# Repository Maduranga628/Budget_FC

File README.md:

# Budget_FC
Low Cost Flight Controller

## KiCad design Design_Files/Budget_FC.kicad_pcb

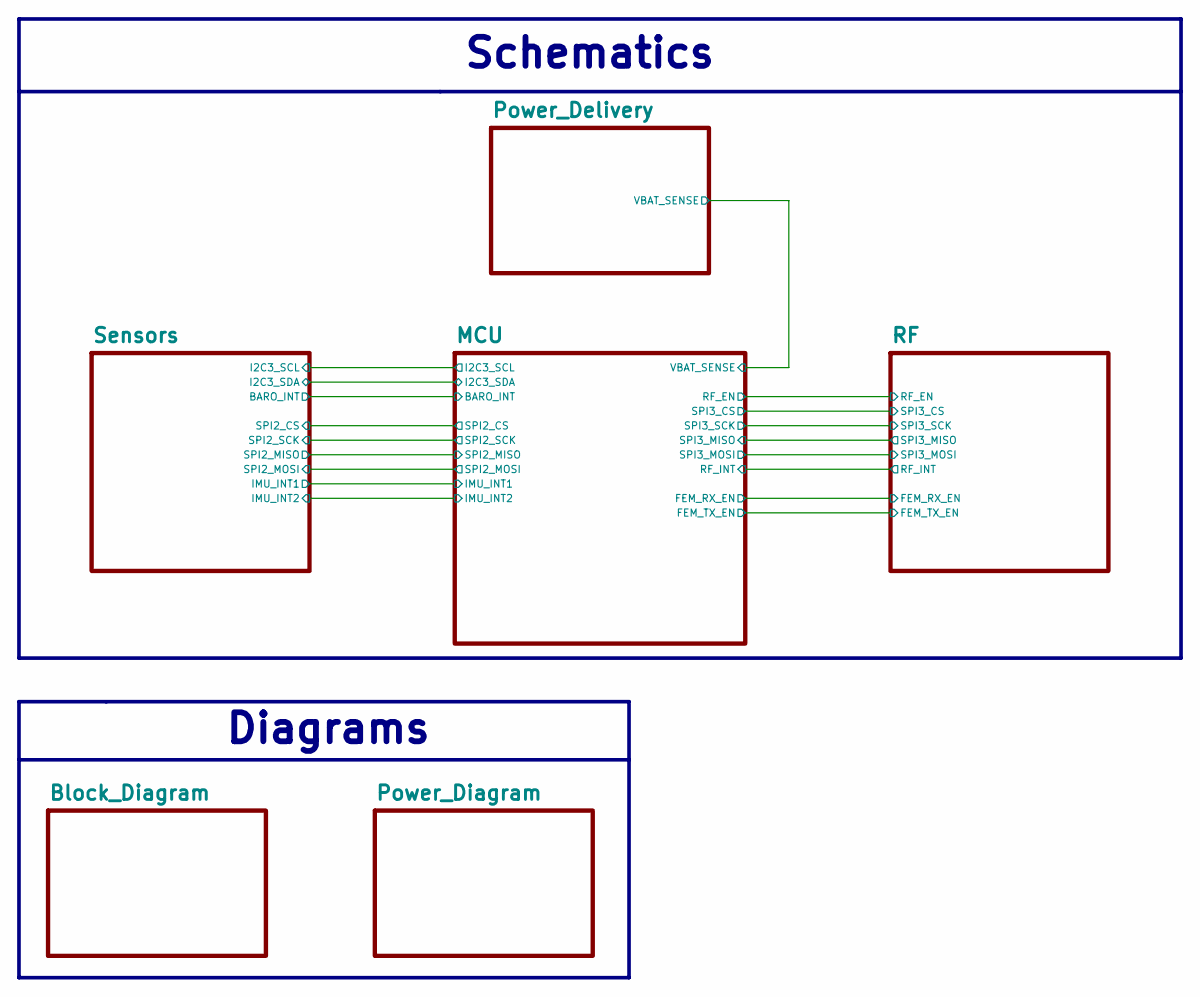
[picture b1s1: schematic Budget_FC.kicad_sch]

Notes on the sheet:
Schematics
Diagrams

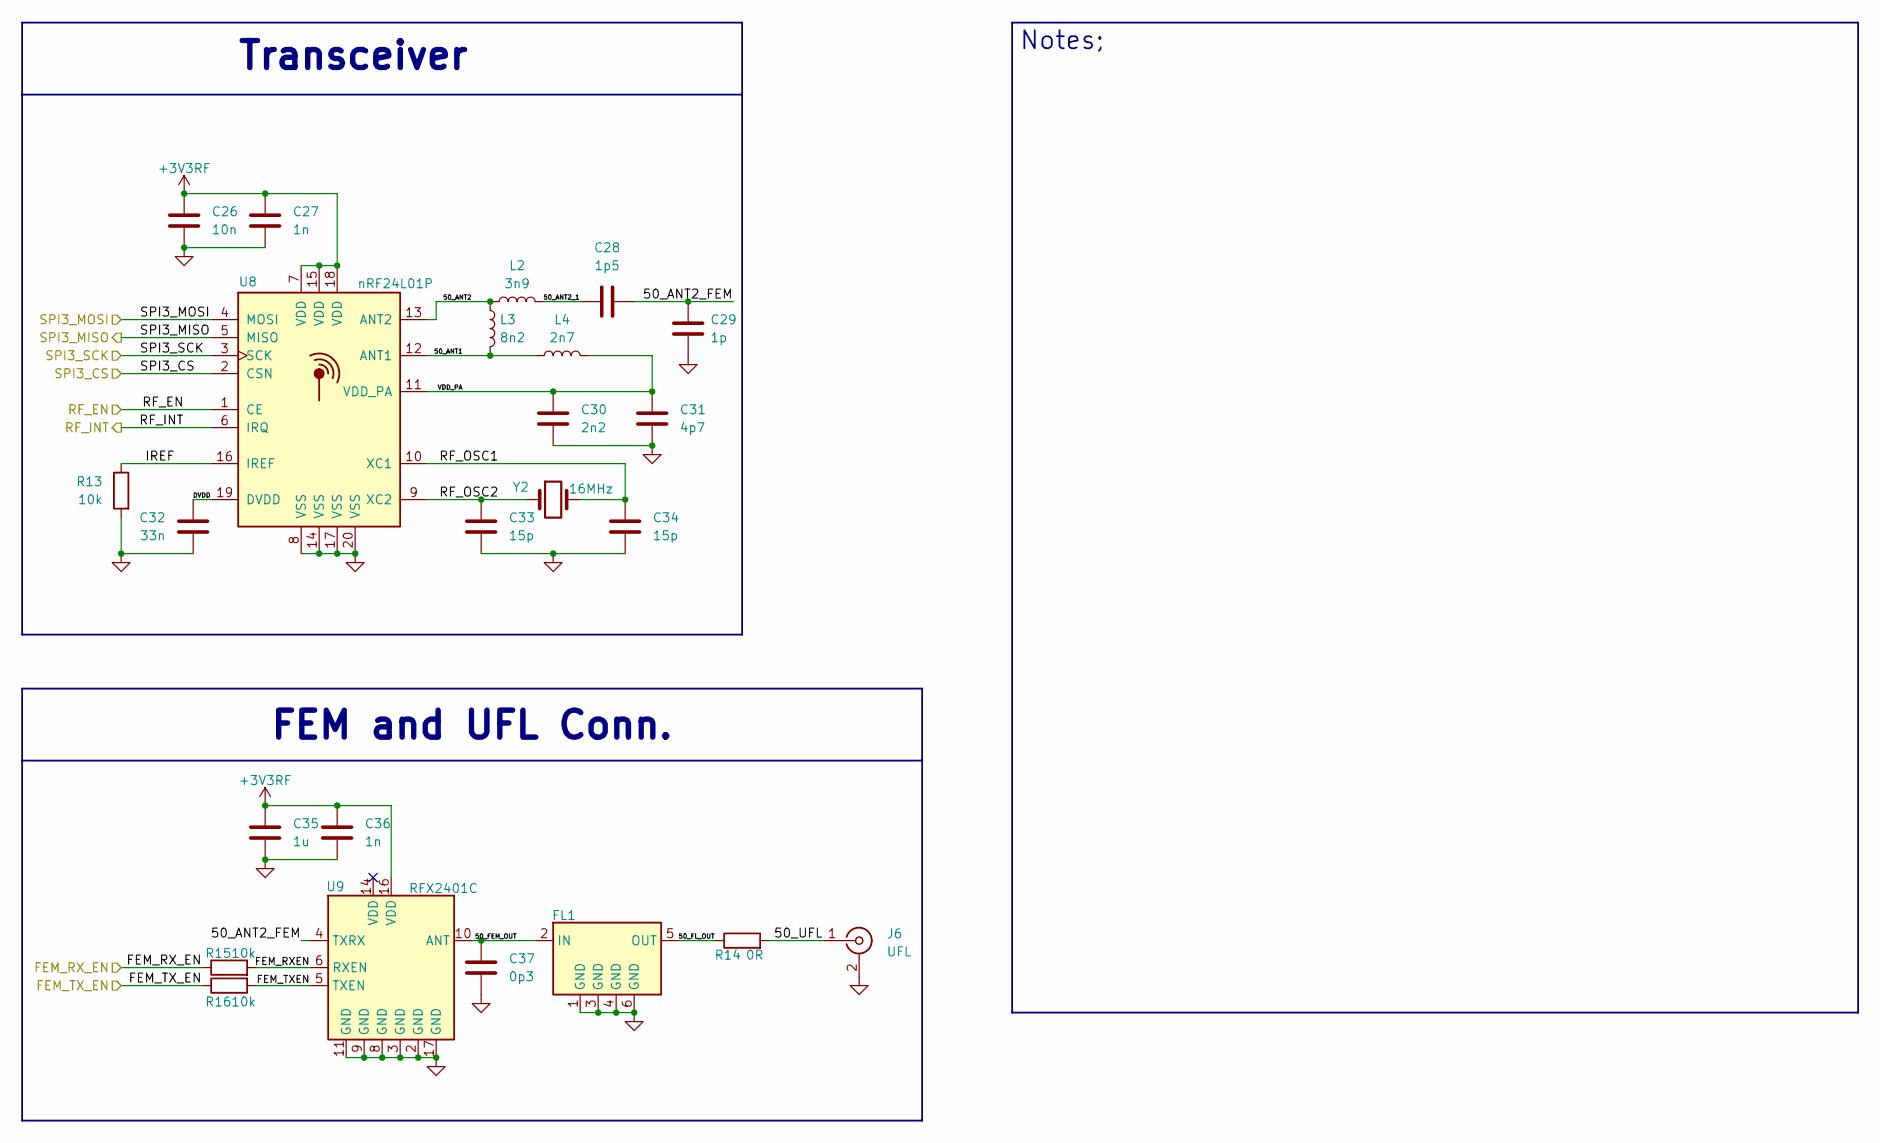
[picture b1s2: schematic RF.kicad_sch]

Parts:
C26: 10n; C_0402_1005Metric_Pad0.74x0.62mm_HandSolder; Manufacturer Part No. CC0402KRX7R9BB103; LCSC No. C60133
C27, C36: 1n; C_0402_1005Metric_Pad0.74x0.62mm_HandSolder; Manufacturer Part No. CC0402KRX7R9BB102; LCSC No. C106205
C28: 1p5; C_0402_1005Metric_Pad0.74x0.62mm_HandSolder; Manufacturer Part No. CC0402CRNPO9BN1R5; LCSC No. C189471
C29: 1p; C_0402_1005Metric_Pad0.74x0.62mm_HandSolder; Manufacturer Part No. CC0402CRNPO9BN1R0; LCSC No. C277493
C30: 2n2; C_0402_1005Metric_Pad0.74x0.62mm_HandSolder; Manufacturer Part No. CC0402KRX7R9BB222; LCSC No. C106861
C31: 4p7; C_0402_1005Metric_Pad0.74x0.62mm_HandSolder; Manufacturer Part No. CC0402CRNPO9BN4R7; LCSC No. C189469
C32: 33n; C_0402_1005Metric_Pad0.74x0.62mm_HandSolder; Manufacturer Part No. CC0402KRX7R9BB333; LCSC No. C106862
C33, C34: 15p; C_0402_1005Metric_Pad0.74x0.62mm_HandSolder; Manufacturer Part No. CC0402FRNPO9BN150; LCSC No. C326803
C35: 1u; C_0603_1608Metric_Pad1.08x0.95mm_HandSolder; Manufacturer Part No. C1608X5R1E105K080AC; Mouser No. 810-C1608X5R1E105K
C37: 0p3; C_0402_1005Metric_Pad0.74x0.62mm_HandSolder; Manufacturer Part No. CQ0402BRNPO9BNR30; LCSC No. C723570
FL1: 2450LP14A0100001T; Balun_Johanson_1.6x0.8mm; Manufacturer Part No. 2450LP14A0100001T; LCSC No. C17651741
J6: UFL; U.FL_Hirose_U.FL-R-SMT-1_Vertical
L2: 3n9; L_0402_1005Metric_Pad0.77x0.64mm_HandSolder; Manufacturer Part No. CS0402-3N9J-S; LCSC No. C329623
L3: 8n2; L_0402_1005Metric_Pad0.77x0.64mm_HandSolder; Manufacturer Part No. CLH1005T-8N2J-S; LCSC No. C108262
L4: 2n7; L_0402_1005Metric_Pad0.77x0.64mm_HandSolder; Manufacturer Part No. CS0402-2N7J-S; LCSC No. C142181
R13: 10k; R_0603_1608Metric_Pad0.98x0.95mm_HandSolder; Manufacturer Part No. RC0603FR-0722KL; LCSC No. C114065
R14: 0R; R_0402_1005Metric_Pad0.72x0.64mm_HandSolder; Manufacturer Part No. RC0402FR-070RL; LCSC No. C106231
R15, R16: 10k; R_0603_1608Metric_Pad0.98x0.95mm_HandSolder; Manufacturer Part No. RC0603FR-0710KL; LCSC No. C98220
U8: nRF24L01P; QFN-20-1EP_4x4mm_P0.5mm_EP2.5x2.5mm; Manufacturer Part No. NRF24L01P-R7; Mouser No. 949-NRF24L01P-R7
U9: RFX2401C; QFN-16-1EP_3x3mm_P0.5mm_EP1.7x1.7mm; Manufacturer Part No. RFX2401C; Mouser No. 477-RFX2401C
Y2: 16MHz; Crystal_SMD_5032-2Pin_5.0x3.2mm; Manufacturer Part No. 0153G2-16.000F12DTLJL; LCSC No. C19674297

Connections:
+3V3RF: C26.1, C27.1, C35.1, C36.1, U8.7 (VDD), U8.15 (VDD), U8.18 (VDD), U9.16 (VDD); also elsewhere on the board
/MCU/FEM_RX_EN: R15.1; also elsewhere on the board
/MCU/FEM_TX_EN: R16.1; also elsewhere on the board
/MCU/RF_EN: U8.1 (CE); also elsewhere on the board
/MCU/RF_INT: U8.6 (IRQ); also elsewhere on the board
/MCU/SPI3_CS: U8.2 (CSN); also elsewhere on the board
/MCU/SPI3_MISO: U8.5 (MISO); also elsewhere on the board
/MCU/SPI3_MOSI: U8.4 (MOSI); also elsewhere on the board
/MCU/SPI3_SCK: U8.3 (SCK); also elsewhere on the board
/RF/50_ANT1: L3.2, L4.1, U8.12 (ANT1)
/RF/50_ANT2: L2.1, L3.1, U8.13 (ANT2)
/RF/50_ANT2_1: C28.1, L2.2
/RF/50_ANT2_FEM: C28.2, C29.1, U9.4 (TXRX)
/RF/50_FEM_OUT: C37.1, FL1.2 (IN), U9.10 (ANT)
/RF/50_FL_OUT: FL1.5 (OUT), R14.1
/RF/50_UFL: J6.1 (In), R14.2
/RF/DVDD: C32.1, U8.19 (DVDD)
/RF/FEM_RXEN: R15.2, U9.6 (RXEN)
/RF/FEM_TXEN: R16.2, U9.5 (TXEN)
/RF/IREF: R13.1, U8.16 (IREF)
/RF/RF_OSC1: C34.1, U8.10 (XC1), Y2.2
/RF/RF_OSC2: C33.1, U8.9 (XC2), Y2.1
/RF/VDD_PA: C30.1, C31.1, L4.2, U8.11 (VDD_PA)
GND: C26.2, C27.2, C29.2, C30.2, C31.2, C32.2, C33.2, C34.2, C35.2, C36.2, C37.2, FL1.1 (GND), FL1.3 (GND), FL1.4 (GND), FL1.6 (GND), J6.2 (Ext), R13.2, U8.8 (VSS), U8.14 (VSS), U8.17 (VSS), U8.20 (VSS), U9.2 (GND), U9.3 (GND), U9.8 (GND), U9.9 (GND), U9.11 (GND), U9.17 (GND); also elsewhere on the board

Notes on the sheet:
Transceiver
FEM and UFL Conn.
Notes;

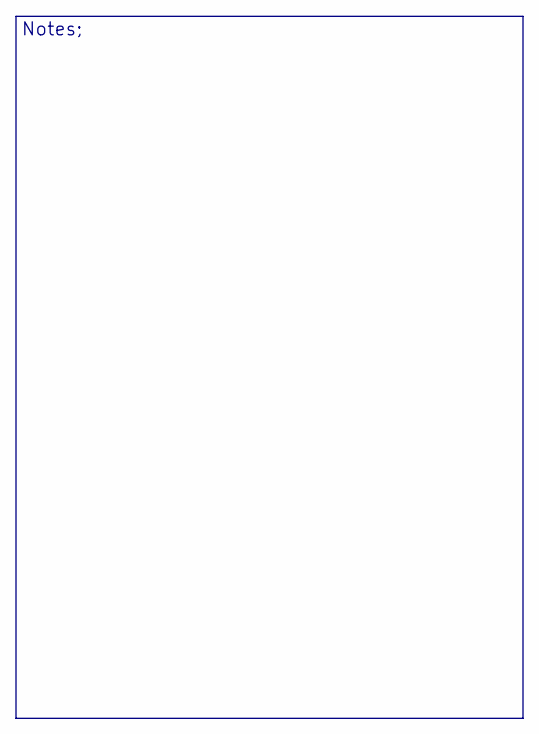
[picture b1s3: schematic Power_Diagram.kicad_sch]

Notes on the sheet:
Notes;

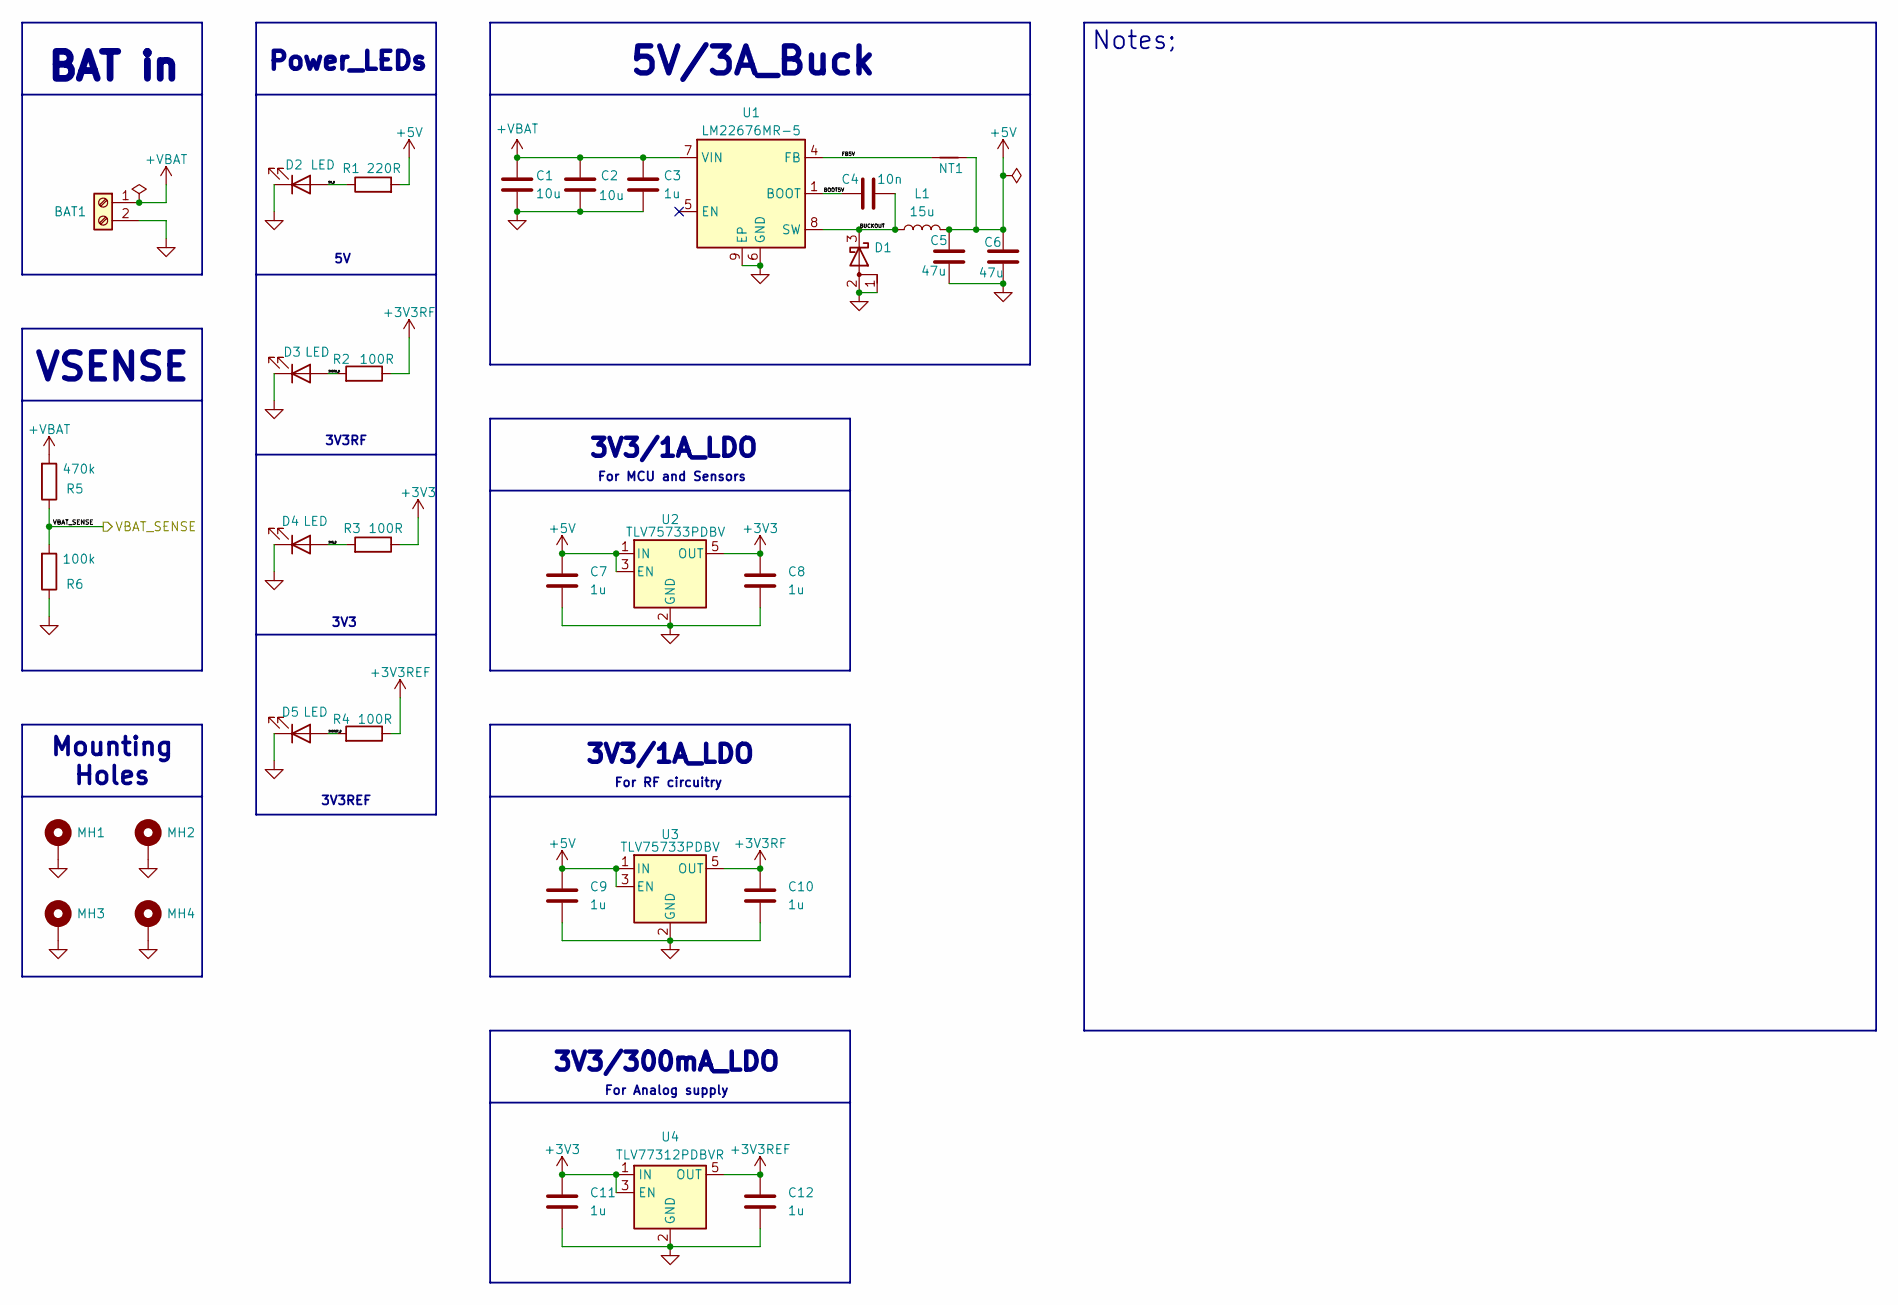
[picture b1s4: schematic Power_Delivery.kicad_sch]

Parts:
BAT1: Screw_Terminal_01x02; TerminalBlock_MaiXu_MX126-5.0-02P_1x02_P5.00mm_3d
C1, C2: 10u; C_1210_3225Metric_Pad1.33x2.70mm_HandSolder; Manufacturer Part No. C3225X7R1H106M250AC; Mouser No. 810-C3225X7R1H106MAC
C3, C7, C8, C9, C10, C11, C12: 1u; C_0603_1608Metric_Pad1.08x0.95mm_HandSolder; Manufacturer Part No. C1608X5R1E105K080AC; Mouser No. 810-C1608X5R1E105K
C4: 10n; C_0603_1608Metric_Pad1.08x0.95mm_HandSolder; Manufacturer Part No. C0603C103K5RACTU; Mouser No. 80-C0603C103K5R
C5, C6: 47u; C_1210_3225Metric_Pad1.33x2.70mm_HandSolder; Manufacturer Part No. GRM32ER61C476KE15L; Mouser No. 81-GRM32ER61C476KE5L
D1: D_Schottky_AAK; Diode_SMD_D_PowerDI-5; Manufacturer Part No. PDS760-13; Mouser No. 621-PDS760-F
D2, D3, D4, D5: LED; LED_0603_1608Metric_Pad1.05x0.95mm_HandSolder; Manufacturer Part No. XL-1608UBC-04; LCSC No. C965807
L1: 15u; L_Bourns_SRP1050WA; Manufacturer Part No. ZD1040-150M; LCSC No. C46956567
MH1, MH2, MH3, MH4: MountingHole_Pad; MountingHole_3.2mm_M3_Pad_Via
NT1: NetTie_2; NetTie-2_SMD_Pad0.5mm
R1: 220R; R_0603_1608Metric_Pad0.98x0.95mm_HandSolder; Manufacturer Part No. RC0603FR-07220RL; LCSC No. C107696
R2, R3, R4: 100R; R_0603_1608Metric_Pad0.98x0.95mm_HandSolder; Manufacturer Part No. RC0603FR-07100RL; LCSC No. C105588
R5: 470k; R_0603_1608Metric_Pad0.98x0.95mm_HandSolder; Manufacturer Part No. RC0603FR-07470KL; LCSC No. C114622
R6: 100k; R_0603_1608Metric_Pad0.98x0.95mm_HandSolder; Manufacturer Part No. RC0603FR-07100KL; LCSC No. C14675
U1: LM22676MR-5; TI_SO-PowerPAD-8; Manufacturer Part No. LM22676QMRX-5.0/NOPB; Mouser No. 926-LM22676QMRX50NPB
U2, U3: TLV75733PDBV; SOT-23-5; Manufacturer Part No. TLV75733PDBVR; Mouser No. 595-TLV75733PDBVR
U4: TLV77312PDBVR; SOT-23-5; Manufacturer Part No. TLV77312PDBVR; Mouser No. 595-TLV77312PDBVR

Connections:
+3V3: C8.1, C11.1, R3.1, U2.5 (OUT), U4.1 (IN), U4.3 (EN); also elsewhere on the board
+3V3REF: C12.1, R4.1, U4.5 (OUT); also elsewhere on the board
+3V3RF: C10.1, R2.1, U3.5 (OUT); also elsewhere on the board
+5V: C5.1, C6.1, C7.1, C9.1, L1.2, NT1.2, R1.2, U2.1 (IN), U2.3 (EN), U3.1 (IN), U3.3 (EN)
+VBAT: BAT1.1, C1.1, C2.1, C3.1, R5.2, U1.7 (VIN)
/MCU/VBAT_SENSE: R5.1, R6.2; also elsewhere on the board
/Power_Delivery/3V3REF_D: D5.2 (A), R4.2; also elsewhere on the board
/Power_Delivery/3V3RF_D: D3.2 (A), R2.2; also elsewhere on the board
/Power_Delivery/3V3_D: D4.2 (A), R3.2; also elsewhere on the board
/Power_Delivery/5V_D: D2.2 (A), R1.1; also elsewhere on the board
/Power_Delivery/BOOT5V: C4.1, U1.1 (BOOT)
/Power_Delivery/BUCKOUT: C4.2, D1.3 (K), L1.1, U1.8 (SW)
/Power_Delivery/FB5V: NT1.1, U1.4 (FB)
GND: BAT1.2, C1.2, C2.2, C3.2, C5.2, C6.2, C7.2, C8.2, C9.2, C10.2, C11.2, C12.2, D1.1 (A), D1.2 (A), D2.1 (K), D3.1 (K), D4.1 (K), D5.1 (K), MH1.1, MH2.1, MH3.1, MH4.1, R6.1, U1.6 (GND), U1.9 (EP), U2.2 (GND), U3.2 (GND), U4.2 (GND); also elsewhere on the board

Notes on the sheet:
3V3/1A_LDO
3V3RF
BAT in
Mounting Holes
3V3REF
Power_LEDs
5V/3A_Buck
For MCU and Sensors
For Analog supply
VSENSE
3V3/300mA_LDO
3V3
For RF circuitry
Notes;

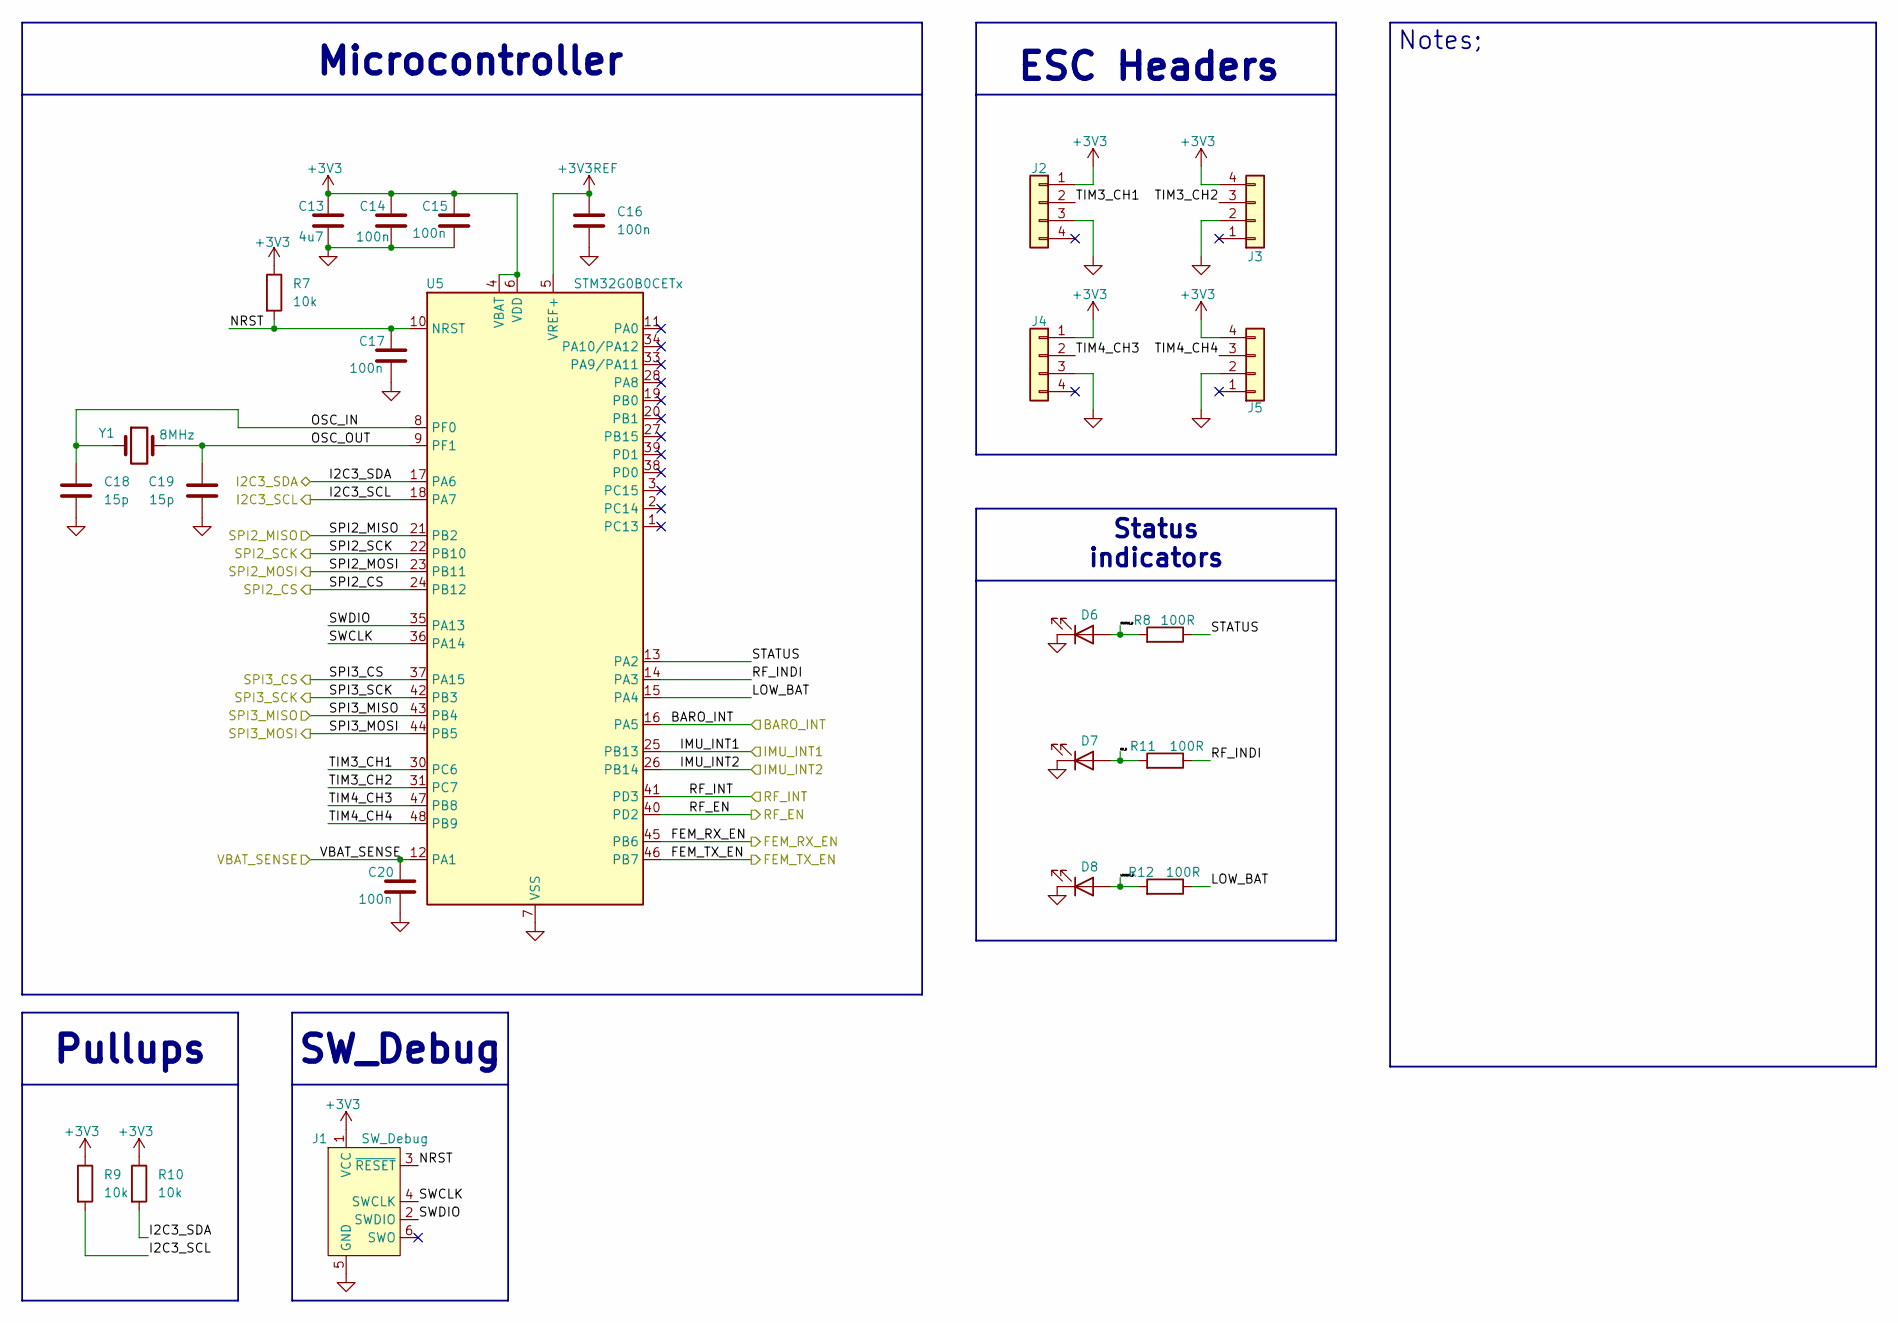
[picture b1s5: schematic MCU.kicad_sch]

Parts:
C13: 4u7; C_0603_1608Metric_Pad1.08x0.95mm_HandSolder; Manufacturer Part No. CC0603KRX5R6BB475; LCSC No. C109456
C14, C15, C16, C17, C20: 100n; C_0603_1608Metric_Pad1.08x0.95mm_HandSolder; Manufacturer Part No. CC0603KRX7R6BB104; LCSC No. C519438
C18, C19: 15p; C_0603_1608Metric_Pad1.08x0.95mm_HandSolder; Manufacturer Part No. CC0603JRNPO9BN150; LCSC No. C107037
D6, D7, D8: LED; LED_0603_1608Metric_Pad1.05x0.95mm_HandSolder; Manufacturer Part No. XL-1608UBC-04; LCSC No. C965807
J1: SW_Debug; Tag-Connect_TC2030-IDC-FP_2x03_P1.27mm_Vertical
J2, J3, J4, J5: Conn_01x04; Molex_KK-254_AE-6410-04A_1x04_P2.54mm_Vertical
R7, R9, R10: 10k; R_0603_1608Metric_Pad0.98x0.95mm_HandSolder; Manufacturer Part No. RC0603FR-0710KL; LCSC No. C98220
R8, R11, R12: 100R; R_0603_1608Metric_Pad0.98x0.95mm_HandSolder; Manufacturer Part No. RC0603FR-07100RL; LCSC No. C105588
U5: STM32G0B0CETx; LQFP-48_7x7mm_P0.5mm; Manufacturer Part No. STM32G0B0CET6TR; Mouser No. 511-STM32G0B0CET6TR
Y1: 8MHz; Crystal_SMD_5032-2Pin_5.0x3.2mm; Manufacturer Part No. XC53G2-8.000-F12NJHP; LCSC No. C2842269

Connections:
+3V3: C13.1, C14.1, C15.1, J1.1 (VCC), J2.1, J3.4, J4.1, J5.4, R7.1, R9.1, R10.1, U5.4 (VBAT), U5.6 (VDD); also elsewhere on the board
+3V3REF: C16.1, U5.5 (VREF+); also elsewhere on the board
/MCU/BARO_INT: U5.16 (PA5); also elsewhere on the board
/MCU/FEM_RX_EN: U5.45 (PB6); also elsewhere on the board
/MCU/FEM_TX_EN: U5.46 (PB7); also elsewhere on the board
/MCU/I2C3_SCL: R9.2, U5.18 (PA7); also elsewhere on the board
/MCU/I2C3_SDA: R10.2, U5.17 (PA6); also elsewhere on the board
/MCU/IMU_INT1: U5.25 (PB13); also elsewhere on the board
/MCU/IMU_INT2: U5.26 (PB14); also elsewhere on the board
/MCU/LOWBAT_D: D8.2 (A), R12.2; also elsewhere on the board
/MCU/LOW_BAT: R12.1, U5.15 (PA4)
/MCU/NRST: C17.1, J1.3 (~RESET), R7.2, U5.10 (NRST); also elsewhere on the board
/MCU/OSC_IN: C18.1, U5.8 (PF0), Y1.1
/MCU/OSC_OUT: C19.1, U5.9 (PF1), Y1.2
/MCU/RF_D: D7.2 (A), R11.2; also elsewhere on the board
/MCU/RF_EN: U5.40 (PD2); also elsewhere on the board
/MCU/RF_INDI: R11.1, U5.14 (PA3)
/MCU/RF_INT: U5.41 (PD3); also elsewhere on the board
/MCU/SPI2_CS: U5.24 (PB12); also elsewhere on the board
/MCU/SPI2_MISO: U5.21 (PB2); also elsewhere on the board
/MCU/SPI2_MOSI: U5.23 (PB11); also elsewhere on the board
/MCU/SPI2_SCK: U5.22 (PB10); also elsewhere on the board
/MCU/SPI3_CS: U5.37 (PA15); also elsewhere on the board
/MCU/SPI3_MISO: U5.43 (PB4); also elsewhere on the board
/MCU/SPI3_MOSI: U5.44 (PB5); also elsewhere on the board
/MCU/SPI3_SCK: U5.42 (PB3); also elsewhere on the board
/MCU/STATUS: R8.1, U5.13 (PA2)
/MCU/STATUS_D: D6.2 (A), R8.2; also elsewhere on the board
/MCU/SWCLK: J1.4 (SWCLK), U5.36 (PA14); also elsewhere on the board
/MCU/SWDIO: J1.2 (SWDIO), U5.35 (PA13); also elsewhere on the board
/MCU/TIM3_CH1: J2.2, U5.30 (PC6)
/MCU/TIM3_CH2: J3.3, U5.31 (PC7)
/MCU/TIM4_CH3: J4.2, U5.47 (PB8)
/MCU/TIM4_CH4: J5.3, U5.48 (PB9)
/MCU/VBAT_SENSE: C20.1, U5.12 (PA1); also elsewhere on the board
GND: C13.2, C14.2, C15.2, C16.2, C17.2, C18.2, C19.2, C20.2, D6.1 (K), D7.1 (K), D8.1 (K), J1.5 (GND), J2.3, J3.2, J4.3, J5.2, U5.7 (VSS); also elsewhere on the board

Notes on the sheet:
Pullups
SW_Debug
ESC Headers
Microcontroller
Status indicators
Notes;

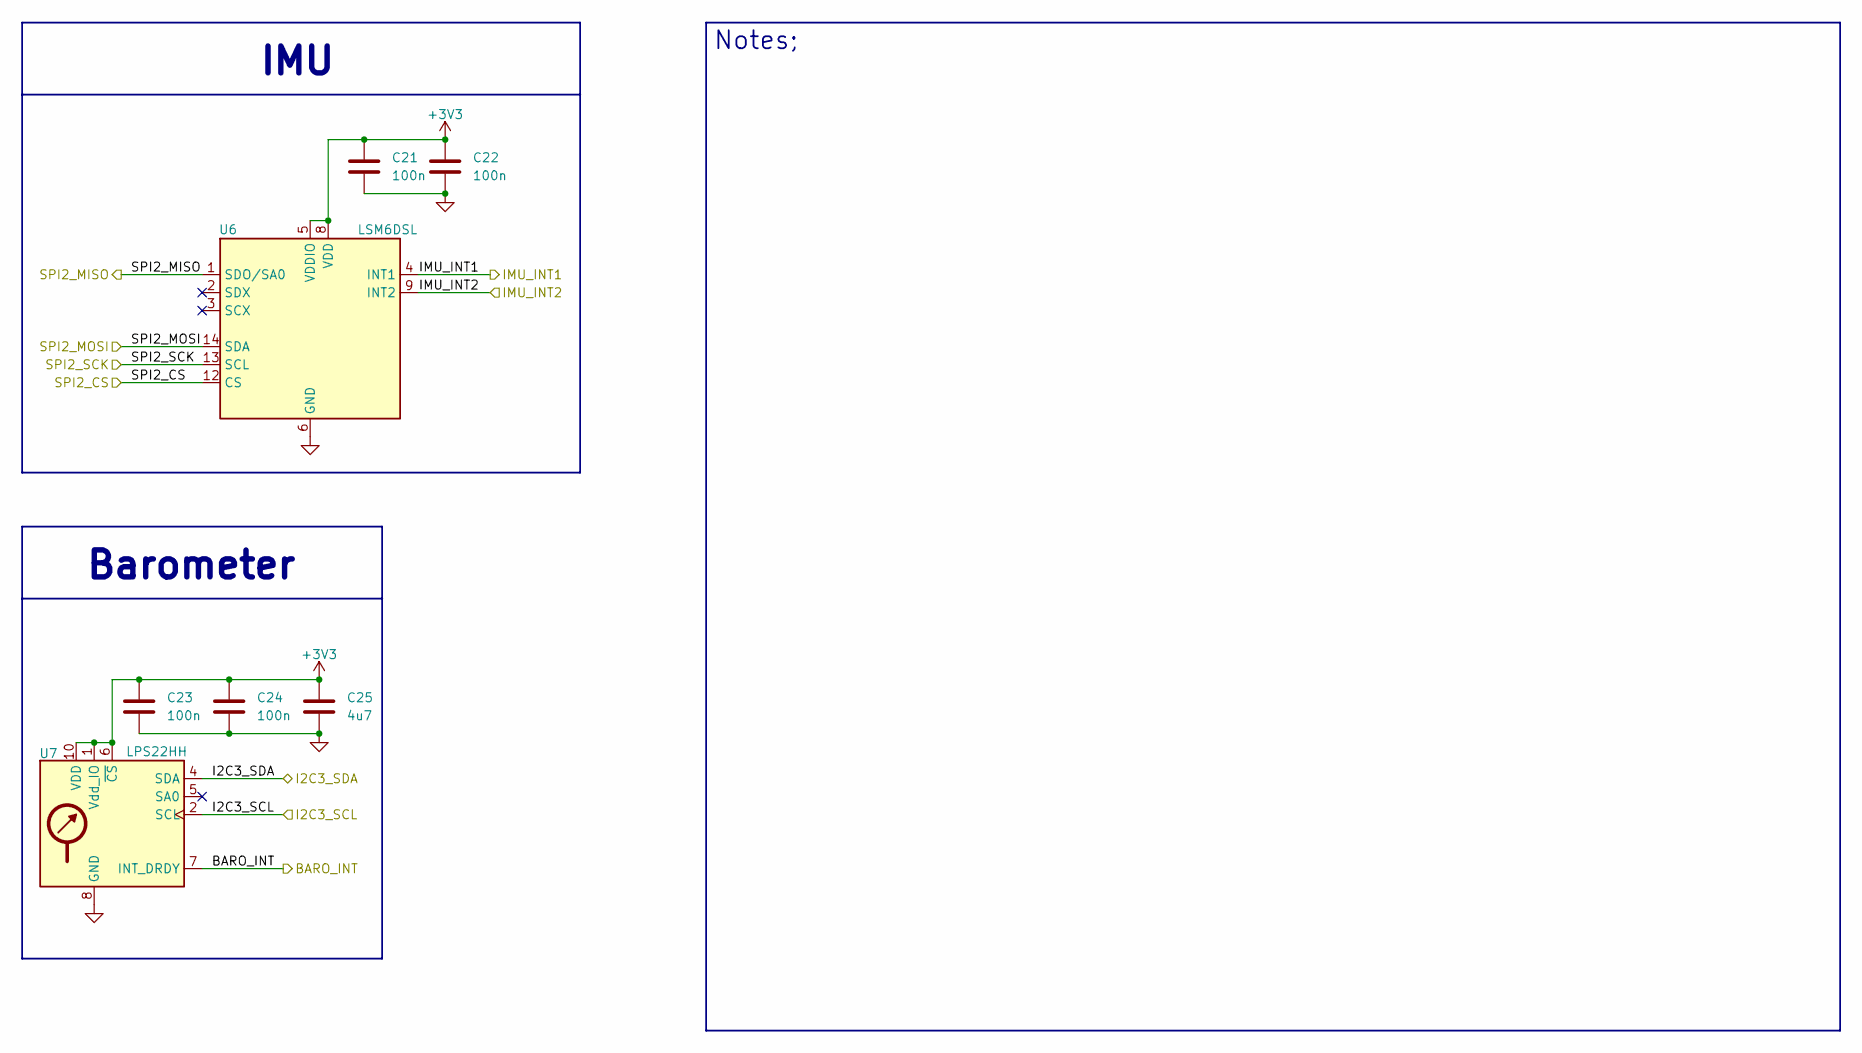
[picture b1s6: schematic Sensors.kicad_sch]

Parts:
C21, C22, C23, C24: 100n; C_0603_1608Metric_Pad1.08x0.95mm_HandSolder; Manufacturer Part No. CC0603KRX7R6BB104; LCSC No. C519438
C25: 4u7; C_0603_1608Metric_Pad1.08x0.95mm_HandSolder; Manufacturer Part No. CC0603KRX5R6BB475; LCSC No. C109456
U6: LSM6DSL; LGA-14_3x2.5mm_P0.5mm_LayoutBorder3x4y; Manufacturer Part No. LSM6DSLTR; Mouser No. 511-LSM6DSLTR
U7: LPS22HH; ST_HLGA-10_2x2mm_P0.5mm_LayoutBorder3x2y; Manufacturer Part No. LPS22HHTR; Mouser No. 511-LPS22HHTR

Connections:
+3V3: C21.1, C22.1, C23.1, C24.1, C25.1, U6.5 (VDDIO), U6.8 (VDD), U7.1 (Vdd_IO), U7.6 (~CS), U7.10 (VDD); also elsewhere on the board
/MCU/BARO_INT: U7.7 (INT_DRDY); also elsewhere on the board
/MCU/I2C3_SCL: U7.2 (SCL); also elsewhere on the board
/MCU/I2C3_SDA: U7.4 (SDA); also elsewhere on the board
/MCU/IMU_INT1: U6.4 (INT1); also elsewhere on the board
/MCU/IMU_INT2: U6.9 (INT2); also elsewhere on the board
/MCU/SPI2_CS: U6.12 (CS); also elsewhere on the board
/MCU/SPI2_MISO: U6.1 (SDO/SA0); also elsewhere on the board
/MCU/SPI2_MOSI: U6.14 (SDA); also elsewhere on the board
/MCU/SPI2_SCK: U6.13 (SCL); also elsewhere on the board
GND: C21.2, C22.2, C23.2, C24.2, C25.2, U6.6 (GND), U6.7 (GND), U7.3 (GND), U7.8 (GND), U7.9 (GND); also elsewhere on the board

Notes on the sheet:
Barometer
IMU
Notes;

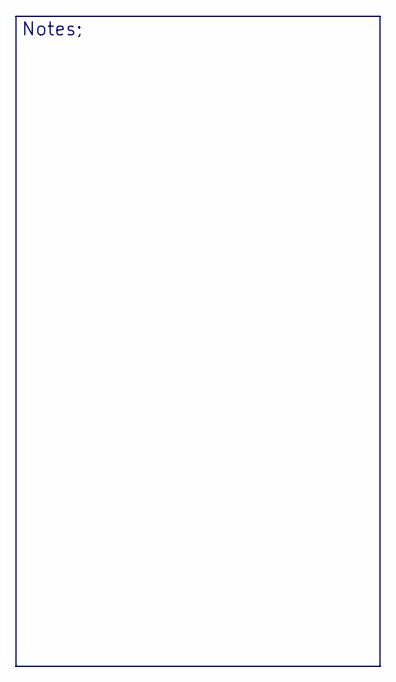
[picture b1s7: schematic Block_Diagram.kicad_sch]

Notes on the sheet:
Notes;

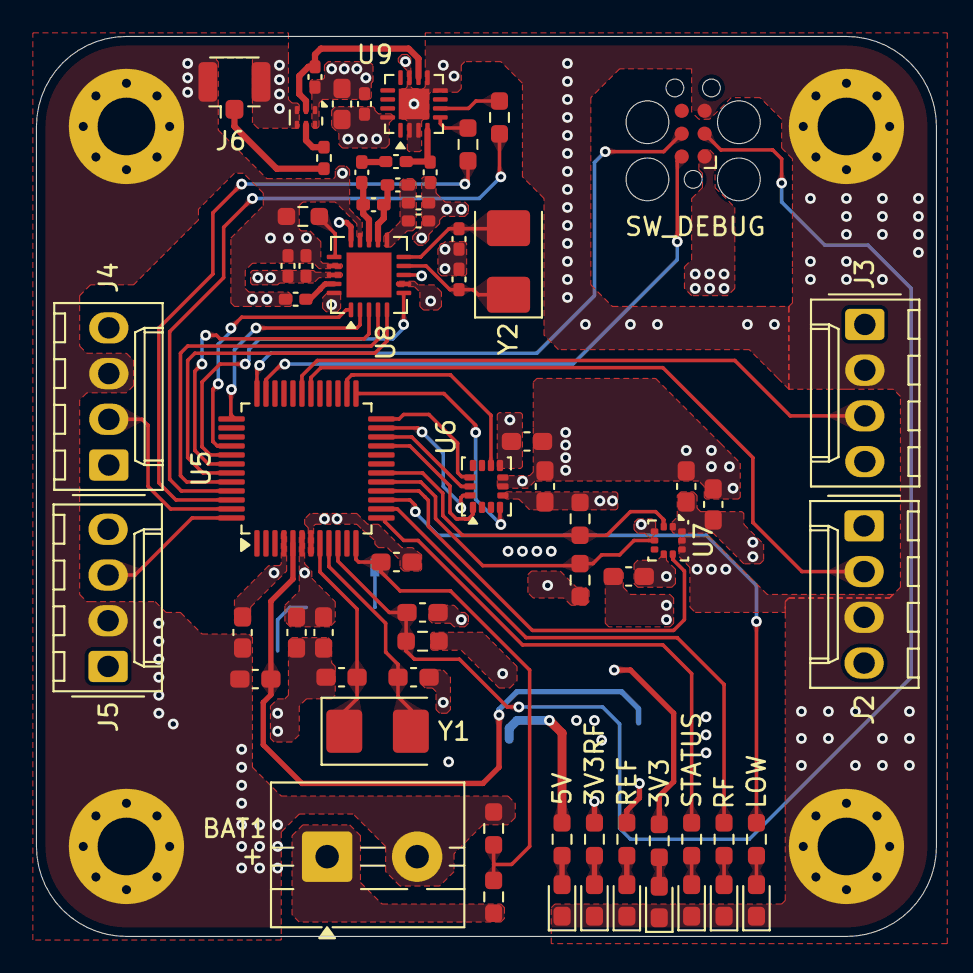
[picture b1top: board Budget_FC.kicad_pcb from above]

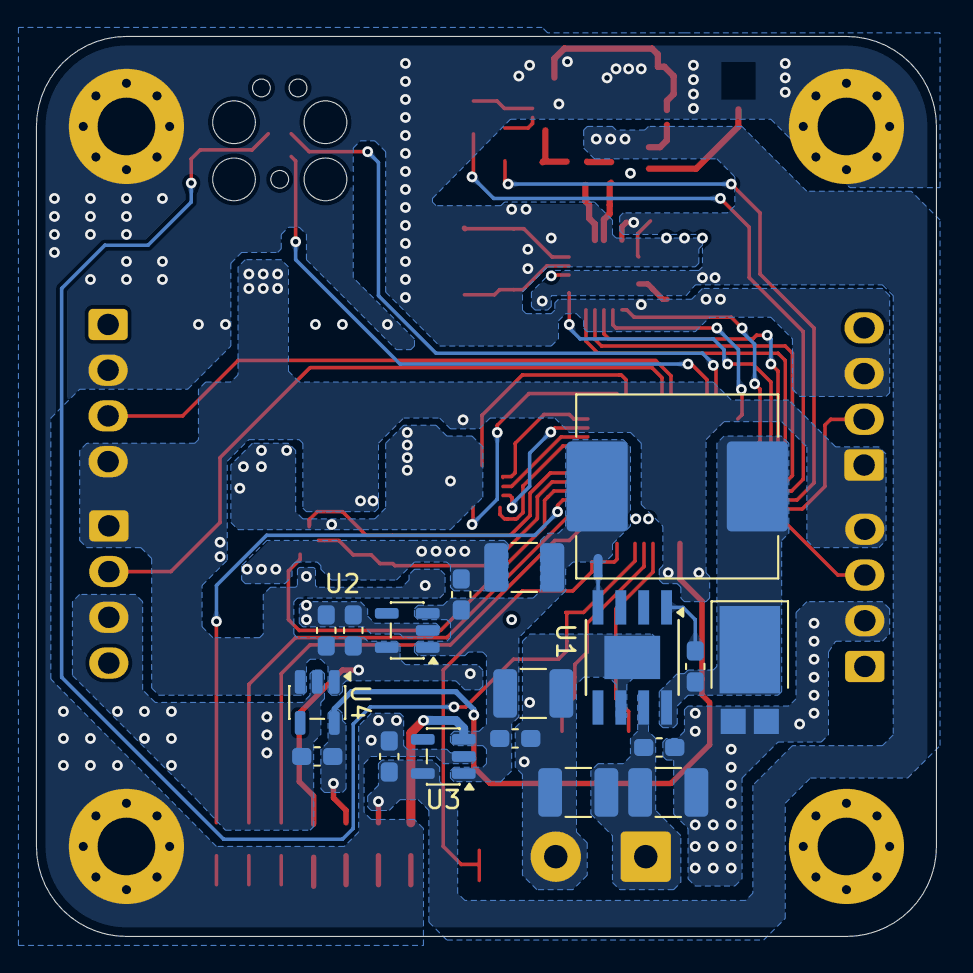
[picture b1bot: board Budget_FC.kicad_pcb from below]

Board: 4 copper layers, 50.0 x 50.0 mm, 89 parts (19 on the bottom side), 60 nets.

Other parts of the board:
3V3, 3V3RF, 5V: LED; LED_0603_1608Metric_Pad1.05x0.95mm_HandSolder
LOW: LED; LED_0603_1608Metric_Pad1.05x0.95mm_HandSolder
REF: LED; LED_0603_1608Metric_Pad1.05x0.95mm_HandSolder
RF: LED; LED_0603_1608Metric_Pad1.05x0.95mm_HandSolder
STATUS: LED; LED_0603_1608Metric_Pad1.05x0.95mm_HandSolder
SW_DEBUG: SW_Debug; Tag-Connect_TC2030-IDC-FP_2x03_P1.27mm_Vertical

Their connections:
+3V3: SW_DEBUG.1 (VCC); also elsewhere on the board
/MCU/LOWBAT_D: LOW.2 (A); also elsewhere on the board
/MCU/NRST: SW_DEBUG.3 (~RESET); also elsewhere on the board
/MCU/RF_D: RF.2 (A); also elsewhere on the board
/MCU/STATUS_D: STATUS.2 (A); also elsewhere on the board
/MCU/SWCLK: SW_DEBUG.4 (SWCLK); also elsewhere on the board
/MCU/SWDIO: SW_DEBUG.2 (SWDIO); also elsewhere on the board
/Power_Delivery/3V3REF_D: REF.2 (A); also elsewhere on the board
/Power_Delivery/3V3RF_D: 3V3RF.2 (A); also elsewhere on the board
/Power_Delivery/3V3_D: 3V3.2 (A); also elsewhere on the board
/Power_Delivery/5V_D: 5V.2 (A); also elsewhere on the board
GND: 3V3.1 (K), 3V3RF.1 (K), 5V.1 (K), LOW.1 (K), REF.1 (K), RF.1 (K), STATUS.1 (K), SW_DEBUG.5 (GND); also elsewhere on the board

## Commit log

2025-12-11 Create temp
